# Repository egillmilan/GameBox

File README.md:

# GameBox
Battery powered pocket device for playing games on. Based on the ATmega328P microcontroller from Atmel, same as is used in the Arduino Uno. Fits in a Hammond 1551k case.

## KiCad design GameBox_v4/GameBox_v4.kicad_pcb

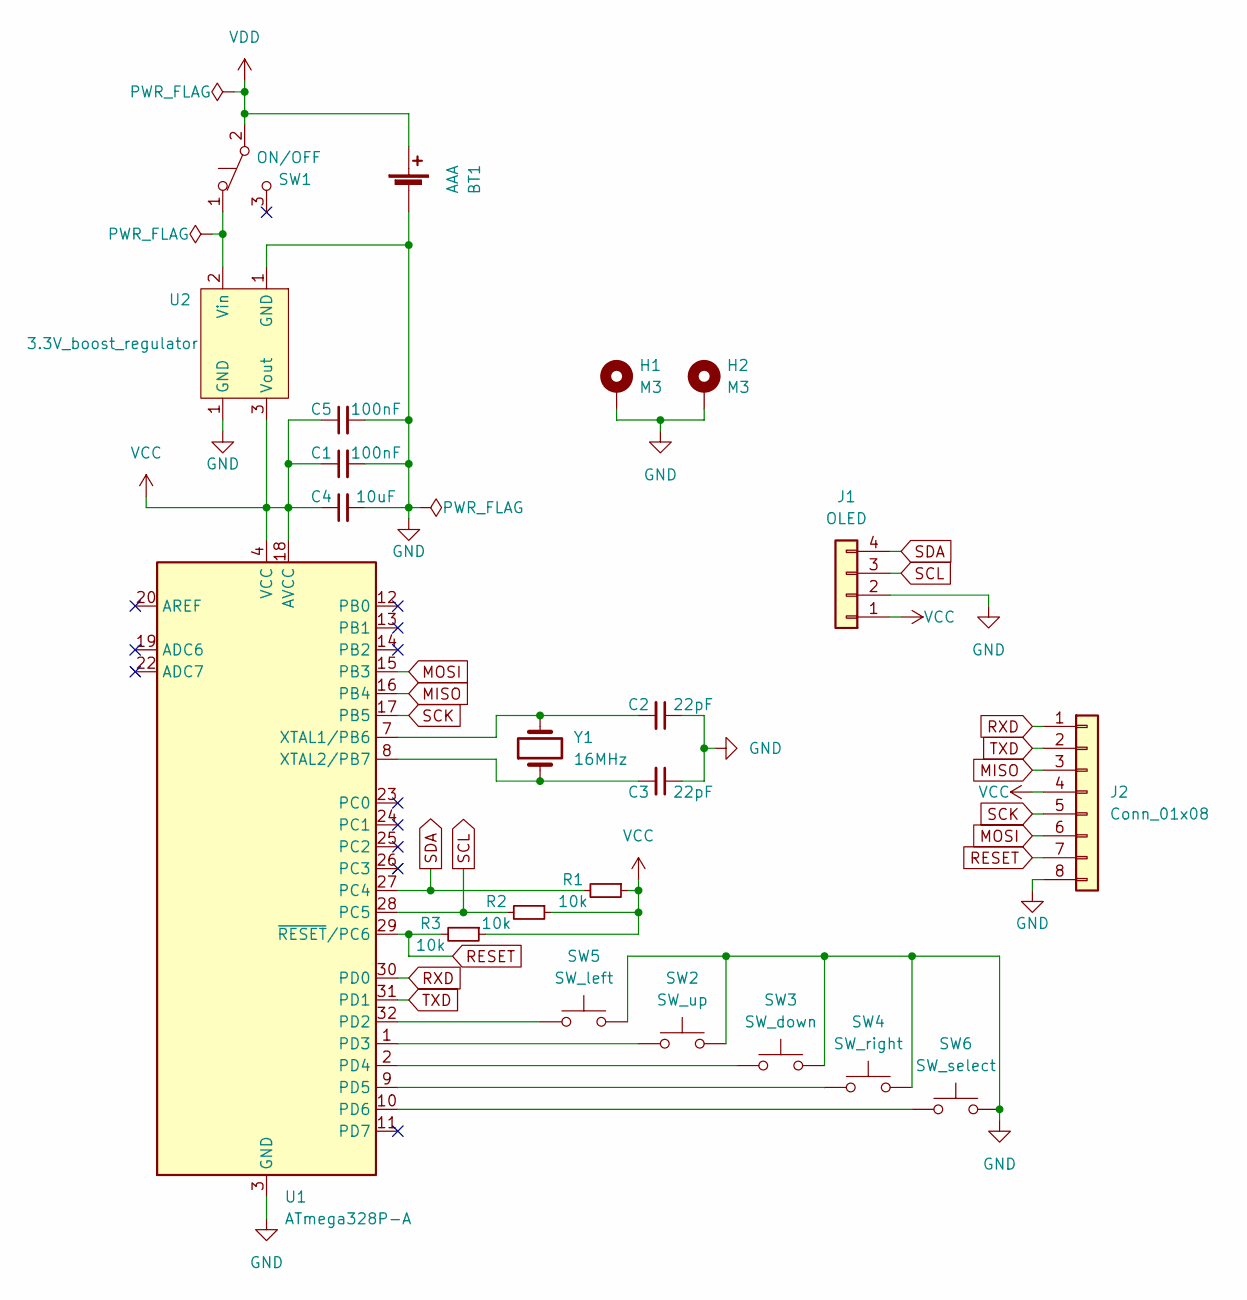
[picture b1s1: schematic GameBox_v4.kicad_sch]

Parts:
BT1: AAA; BK-82_AAA_battery_holder
C1, C5: 100nF; C_0805_2012Metric_Pad1.18x1.45mm_HandSolder
C2, C3: 22pF; C_0805_2012Metric_Pad1.18x1.45mm_HandSolder
C4: 10uF; C_0805_2012Metric_Pad1.18x1.45mm_HandSolder
H1, H2: M3; MountingHole_3.2mm_M3_Pad_Via
J1: OLED; 1.3_inch_OLED_IIC
J2: Conn_01x08; PinHeader_2x04_P2.54mm_Vertical
R1, R2, R3: 10k; R_0805_2012Metric_Pad1.20x1.40mm_HandSolder
SW1: ON/OFF; SS12D10
SW2: SW_up; SW_PUSH_6mm_H9.5mm
SW3: SW_down; SW_PUSH_6mm_H9.5mm
SW4: SW_right; SW_PUSH_6mm_H9.5mm
SW5: SW_left; SW_PUSH_6mm_H9.5mm
SW6: SW_select; SW_PUSH_6mm_H9.5mm
U1: ATmega328P-A; TQFP-32_7x7mm_P0.8mm
U2: 3.3V_boost_regulator; 3.3V_boost_regulator_castellated
Y1: 16MHz; Crystal_HC49-4H_Vertical

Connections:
GND: BT1.2 (-), C1.2, C2.1, C3.1, C4.2, C5.2, H1.1, H2.1, J1.2, J2.8, SW2.2, SW3.2, SW4.2, SW5.2, SW6.2, U1.3 (GND), U1.5 (GND), U1.21 (GND), U2.1 (GND)
MISO: J2.3, U1.16 (PB4)
MOSI: J2.6, U1.15 (PB3)
unnamed: C2.2, U1.7 (XTAL1/PB6), Y1.2
unnamed: C3.2, U1.8 (XTAL2/PB7), Y1.1
unnamed: SW1.1 (A), U2.2 (Vin)
unnamed: SW2.1, U1.1 (PD3)
unnamed: SW3.1, U1.2 (PD4)
unnamed: SW4.1, U1.9 (PD5)
unnamed: SW5.1, U1.32 (PD2)
unnamed: SW6.1, U1.10 (PD6)
RESET: J2.7, R3.2, U1.29 (~RESET/PC6)
RXD: J2.1, U1.30 (PD0)
SCK: J2.5, U1.17 (PB5)
SCL: J1.3, R2.2, U1.28 (PC5)
SDA: J1.4, R1.2, U1.27 (PC4)
TXD: J2.2, U1.31 (PD1)
VCC: C1.1, C4.1, C5.1, J1.1, J2.4, R1.1, R2.1, R3.1, U1.4 (VCC), U1.6 (VCC), U1.18 (AVCC), U2.3 (Vout)
VDD: BT1.1 (+), SW1.2 (B)

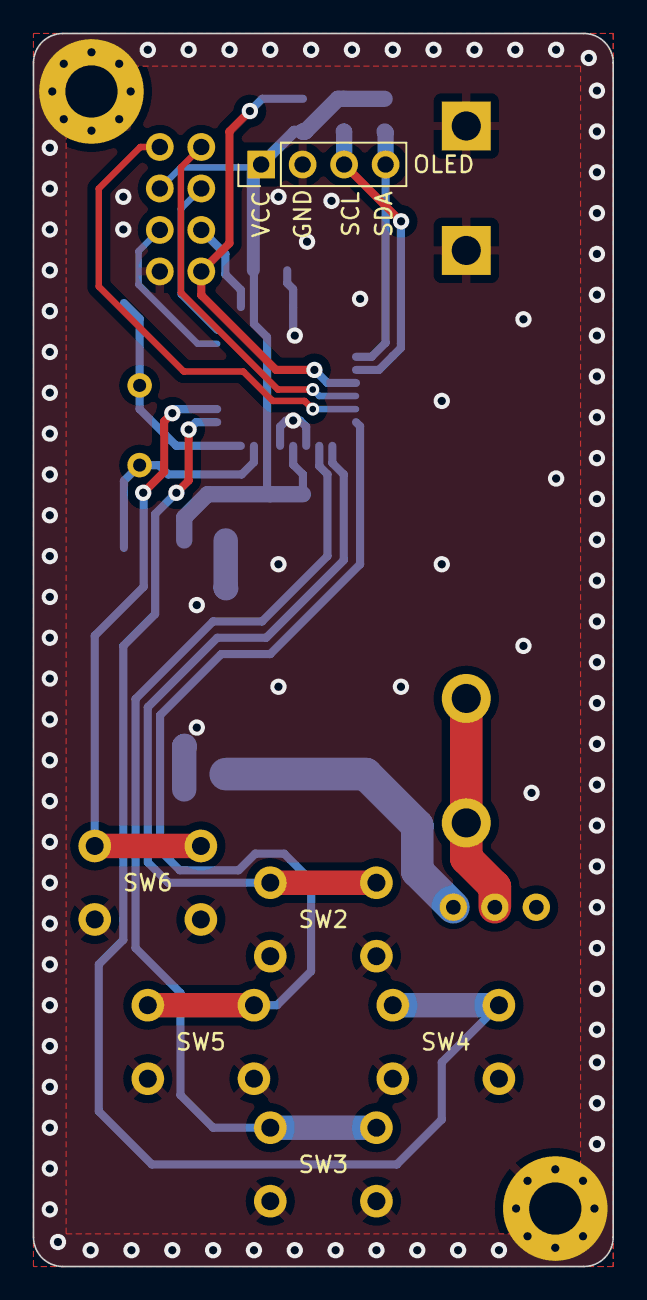
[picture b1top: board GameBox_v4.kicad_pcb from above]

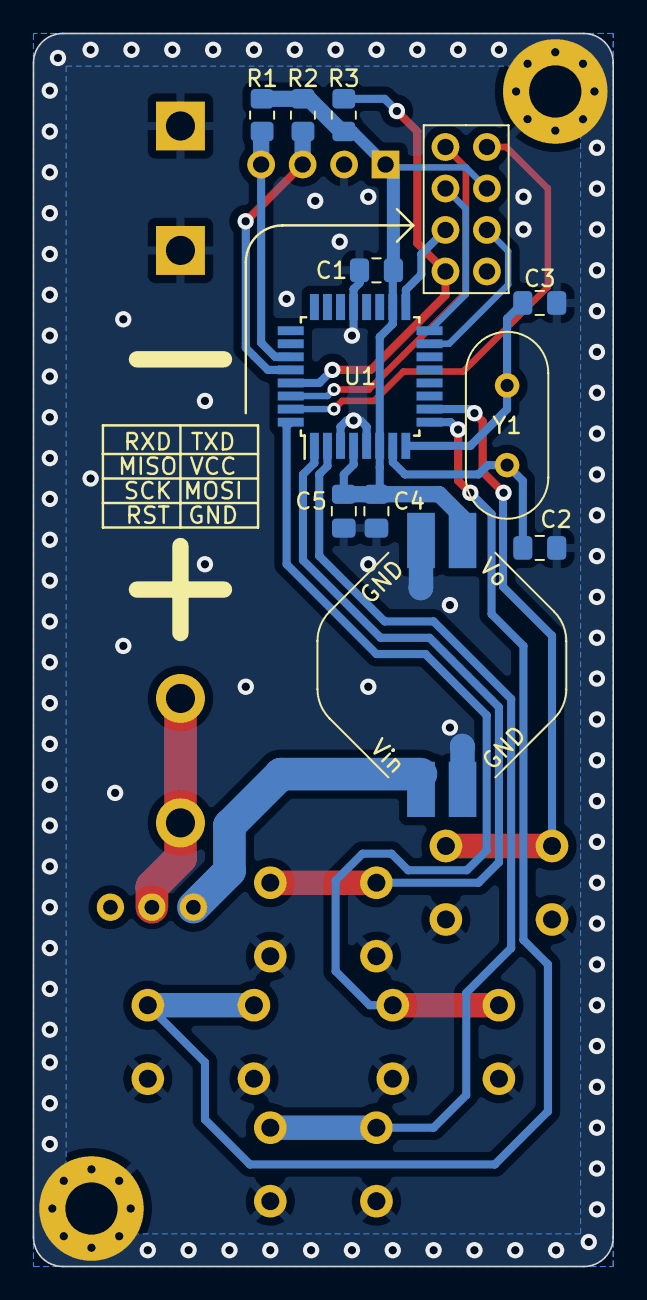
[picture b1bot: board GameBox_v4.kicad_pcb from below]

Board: 2 copper layers, 35.5 x 75.5 mm, 22 parts (13 on the bottom side), 19 nets.

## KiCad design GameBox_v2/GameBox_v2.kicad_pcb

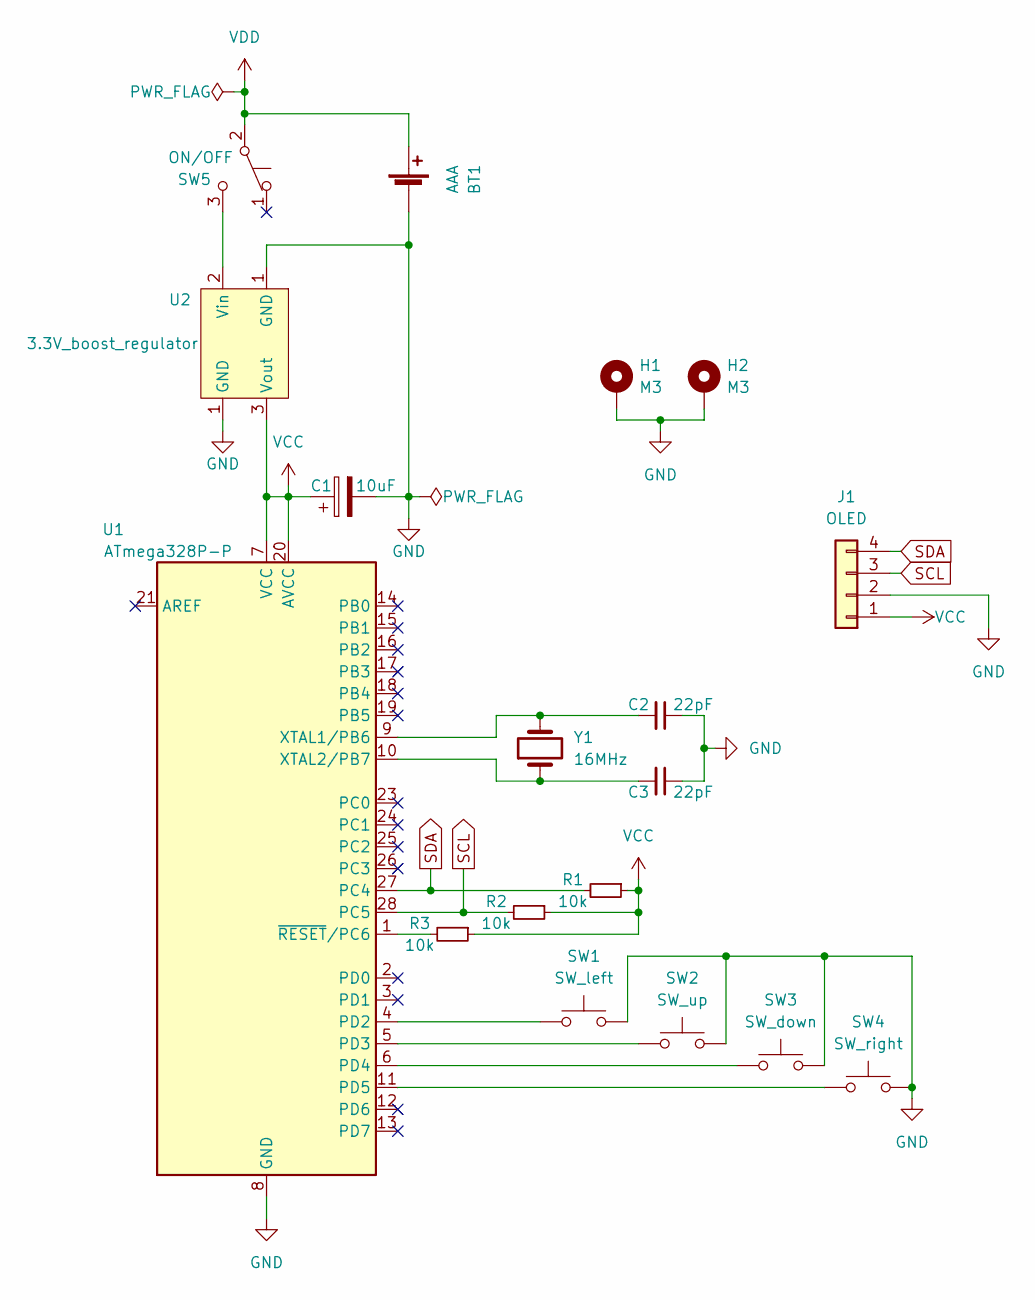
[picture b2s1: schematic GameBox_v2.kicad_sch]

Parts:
BT1: AAA; BK-82_AAA_battery_holder
C1: 10uF; C_0805_2012Metric_Pad1.18x1.45mm_HandSolder
C2, C3: 22pF; C_0805_2012Metric_Pad1.18x1.45mm_HandSolder
H1, H2: M3; MountingHole_3.2mm_M3_Pad_Via
J1: OLED; 1.3_inch_OLED_IIC
R1, R2, R3: 10k; R_0805_2012Metric_Pad1.20x1.40mm_HandSolder
SW1: SW_left; SW_PUSH_6mm_H9.5mm
SW2: SW_up; SW_PUSH_6mm_H9.5mm
SW3: SW_down; SW_PUSH_6mm_H9.5mm
SW4: SW_right; SW_PUSH_6mm_H9.5mm
SW5: ON/OFF; EG1218
U1: ATmega328P-P; DIP-28_W7.62mm
U2: 3.3V_boost_regulator
Y1: 16MHz; Crystal_HC49-4H_Vertical

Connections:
GND: BT1.2 (-), C1.2, C2.1, C3.1, H1.1, H2.1, J1.2, SW1.2, SW2.2, SW3.2, SW4.2, U1.8 (GND), U1.22 (GND), U2.1 (GND)
unnamed: C2.2, U1.9 (XTAL1/PB6), Y1.2
unnamed: C3.2, U1.10 (XTAL2/PB7), Y1.1
unnamed: R3.2, U1.1 (~RESET/PC6)
unnamed: SW1.1, U1.4 (PD2)
unnamed: SW2.1, U1.5 (PD3)
unnamed: SW3.1, U1.6 (PD4)
unnamed: SW4.1, U1.11 (PD5)
unnamed: SW5.3 (C), U2.2 (Vin)
SCL: J1.3, R2.2, U1.28 (PC5)
SDA: J1.4, R1.2, U1.27 (PC4)
VCC: C1.1, J1.1, R1.1, R2.1, R3.1, U1.7 (VCC), U1.20 (AVCC), U2.3 (Vout)
VDD: BT1.1 (+), SW5.2 (B)

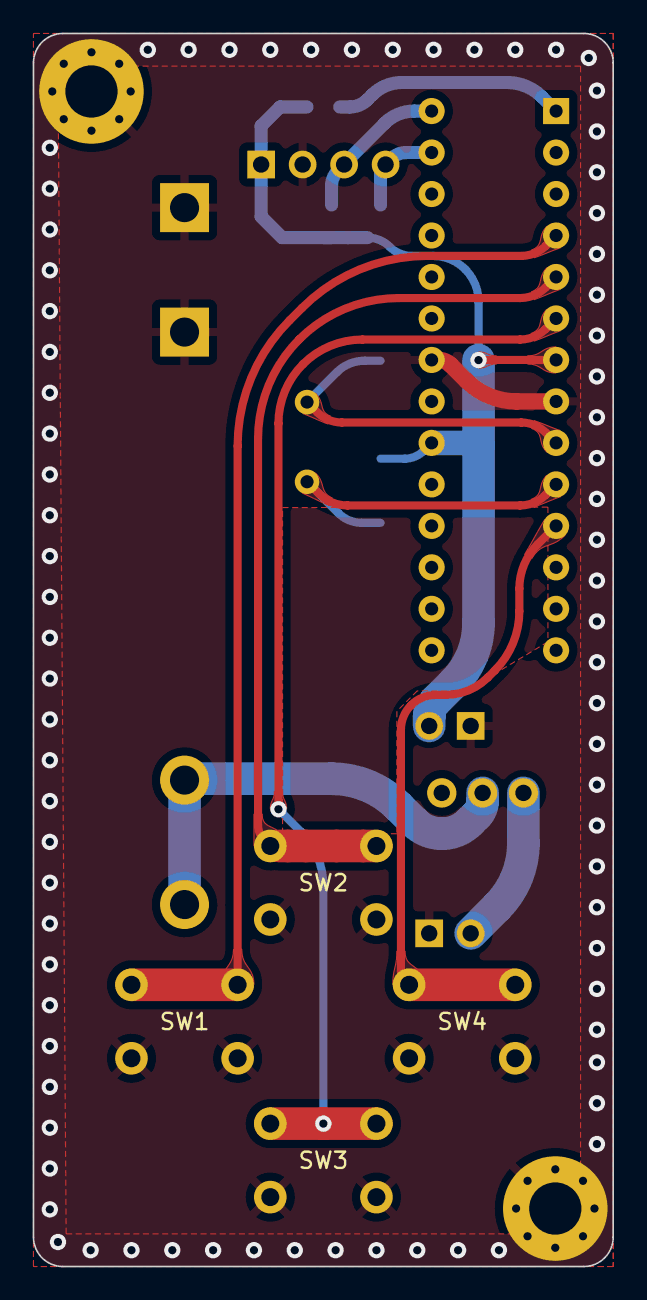
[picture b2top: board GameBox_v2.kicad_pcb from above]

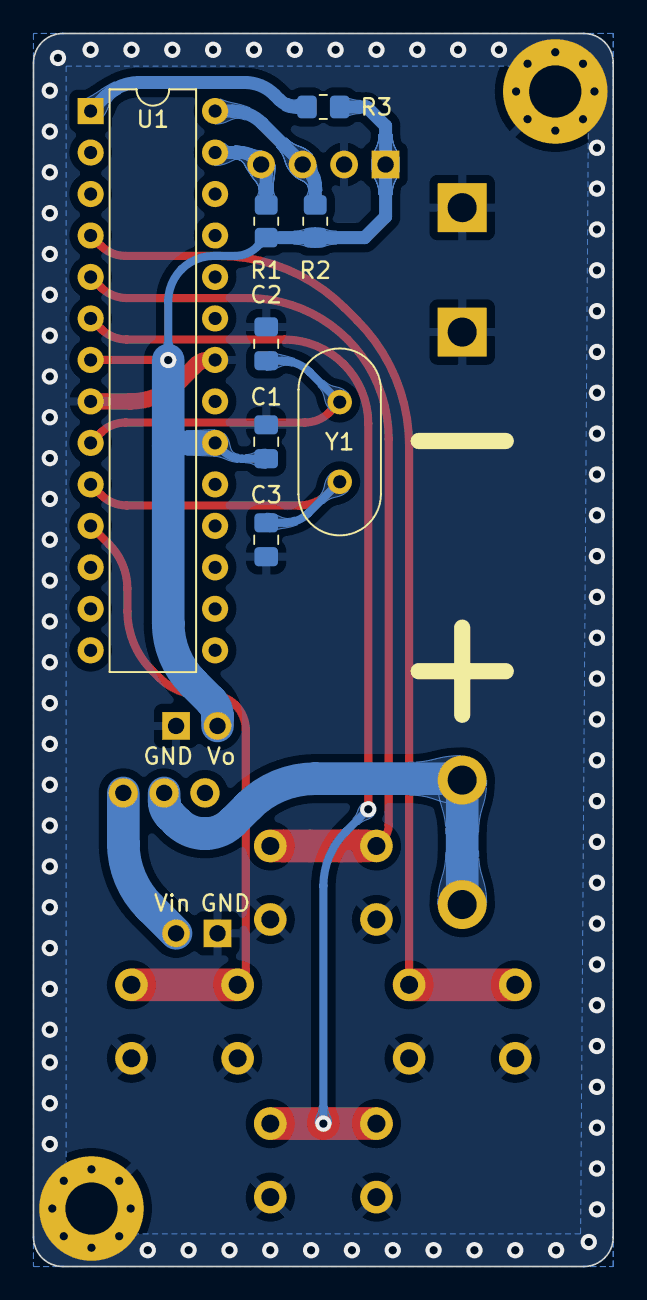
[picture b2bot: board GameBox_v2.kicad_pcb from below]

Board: 2 copper layers, 35.5 x 75.5 mm, 18 parts (10 on the bottom side), 13 nets.

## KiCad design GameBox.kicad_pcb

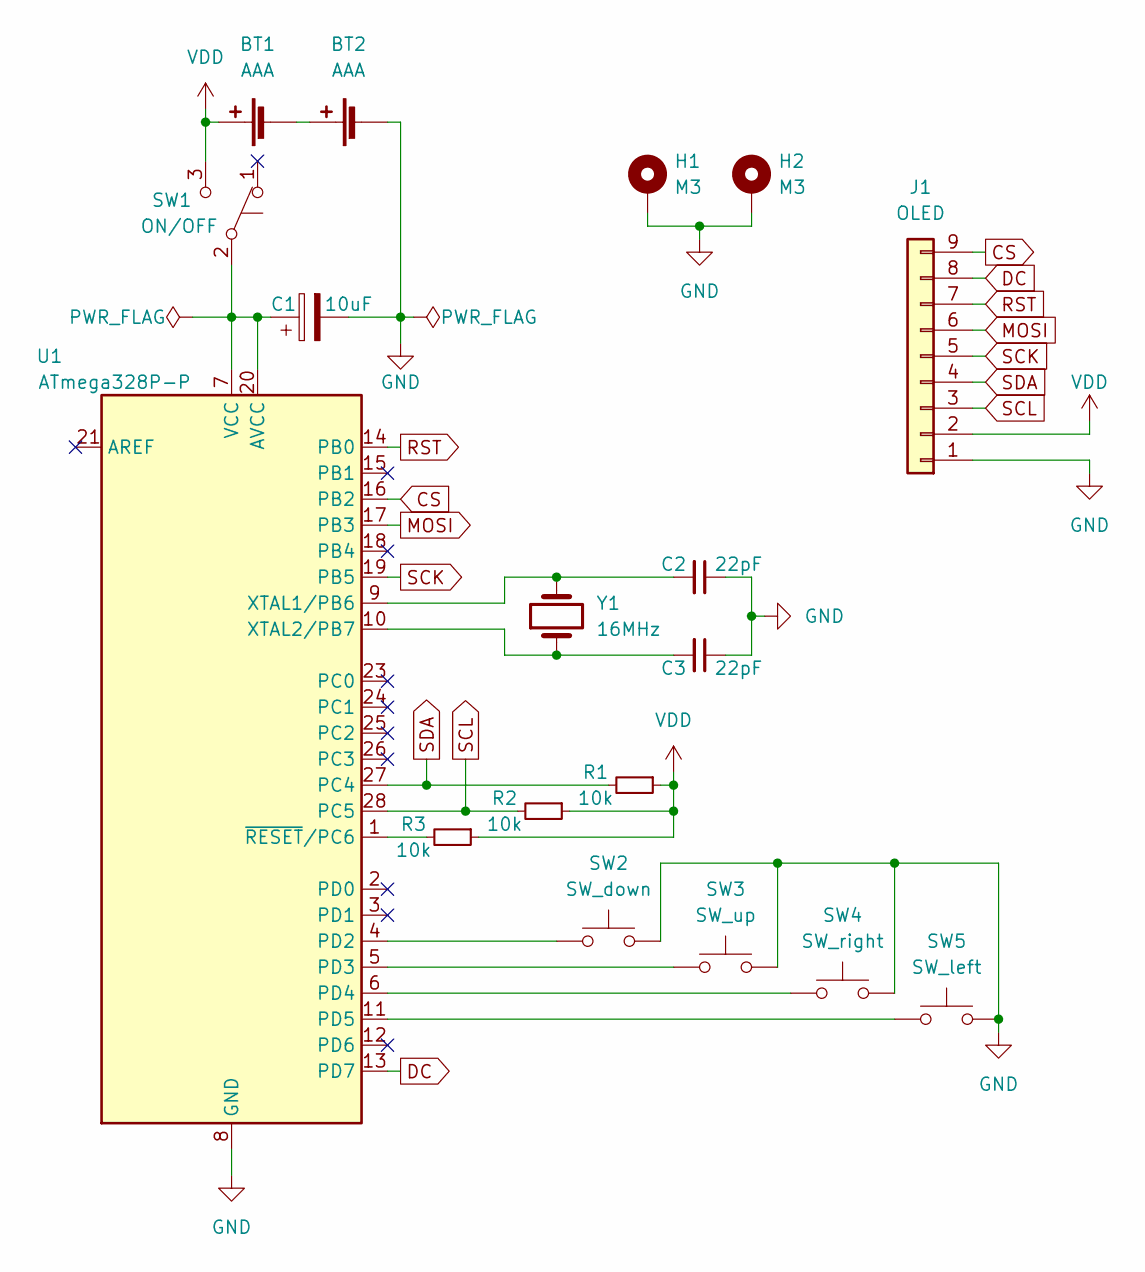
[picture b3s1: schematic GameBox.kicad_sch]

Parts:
BT1, BT2: AAA; BK-82_AAA_battery_holder
C1: 10uF; CP_Radial_D4.0mm_P1.50mm
C2, C3: 22pF; C_Disc_D4.3mm_W1.9mm_P5.00mm
H1, H2: M3; MountingHole_3.2mm_M3_Pad_TopBottom
J1: OLED; 1.3_inch_OLED_IIC
R1, R2, R3: 10k; R_Axial_DIN0207_L6.3mm_D2.5mm_P10.16mm_Horizontal
SW1: ON/OFF; SS12D10
SW2: SW_down; SW_PUSH_6mm_H9.5mm
SW3: SW_up; SW_PUSH_6mm_H9.5mm
SW4: SW_right; SW_PUSH_6mm_H9.5mm
SW5: SW_left; SW_PUSH_6mm_H9.5mm
U1: ATmega328P-P; DIP-28_W7.62mm
Y1: 16MHz; Crystal_HC49-4H_Vertical

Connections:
CS: J1.9, U1.16 (PB2)
DC: J1.8, U1.13 (PD7)
GND: BT2.2 (-), C1.2, C2.1, C3.1, H1.1, H2.1, J1.1, SW2.2, SW3.2, SW4.2, SW5.2, U1.8 (GND), U1.22 (GND)
MOSI: J1.6, U1.17 (PB3)
unnamed: BT1.2 (-), BT2.1 (+)
unnamed: C1.1, SW1.2 (B), U1.7 (VCC), U1.20 (AVCC)
unnamed: C2.2, U1.9 (XTAL1/PB6), Y1.2
unnamed: C3.2, U1.10 (XTAL2/PB7), Y1.1
unnamed: R3.2, U1.1 (~RESET/PC6)
unnamed: SW2.1, U1.4 (PD2)
unnamed: SW3.1, U1.5 (PD3)
unnamed: SW4.1, U1.6 (PD4)
unnamed: SW5.1, U1.11 (PD5)
RST: J1.7, U1.14 (PB0)
SCK: J1.5, U1.19 (PB5)
SCL: J1.3, R2.2, U1.28 (PC5)
SDA: J1.4, R1.2, U1.27 (PC4)
VDD: BT1.1 (+), J1.2, R1.1, R2.1, R3.1, SW1.3 (C)

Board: 2 copper layers, 18 parts (9 on the bottom side), 18 nets, no tracks yet.

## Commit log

2022-04-01 Component placement
2022-04-02 Finished PCB design
    Finished PCB design and schematic
2022-04-03 Library updates
2022-04-04 Version 2 designed
    Version 2 uses a single cell and a boost converter. Version 2 uses a few SMD components in order to reduce the clutter on the PCB and the SPI bus was ditched in V2 as well.
2022-04-04 Added images
2022-04-11 Version 3 added and minor fixes to v2
2022-04-16 Added v4
    v4 supports the castellated version of the 3.3V boost regulator for a slightly cleaner PCB with more surface mounted components
2022-04-16 Cleanup
2022-04-28 Rounded tracks and teardrops
2022-04-28 Footprint updates
2022-05-20 fixed OLEDs
